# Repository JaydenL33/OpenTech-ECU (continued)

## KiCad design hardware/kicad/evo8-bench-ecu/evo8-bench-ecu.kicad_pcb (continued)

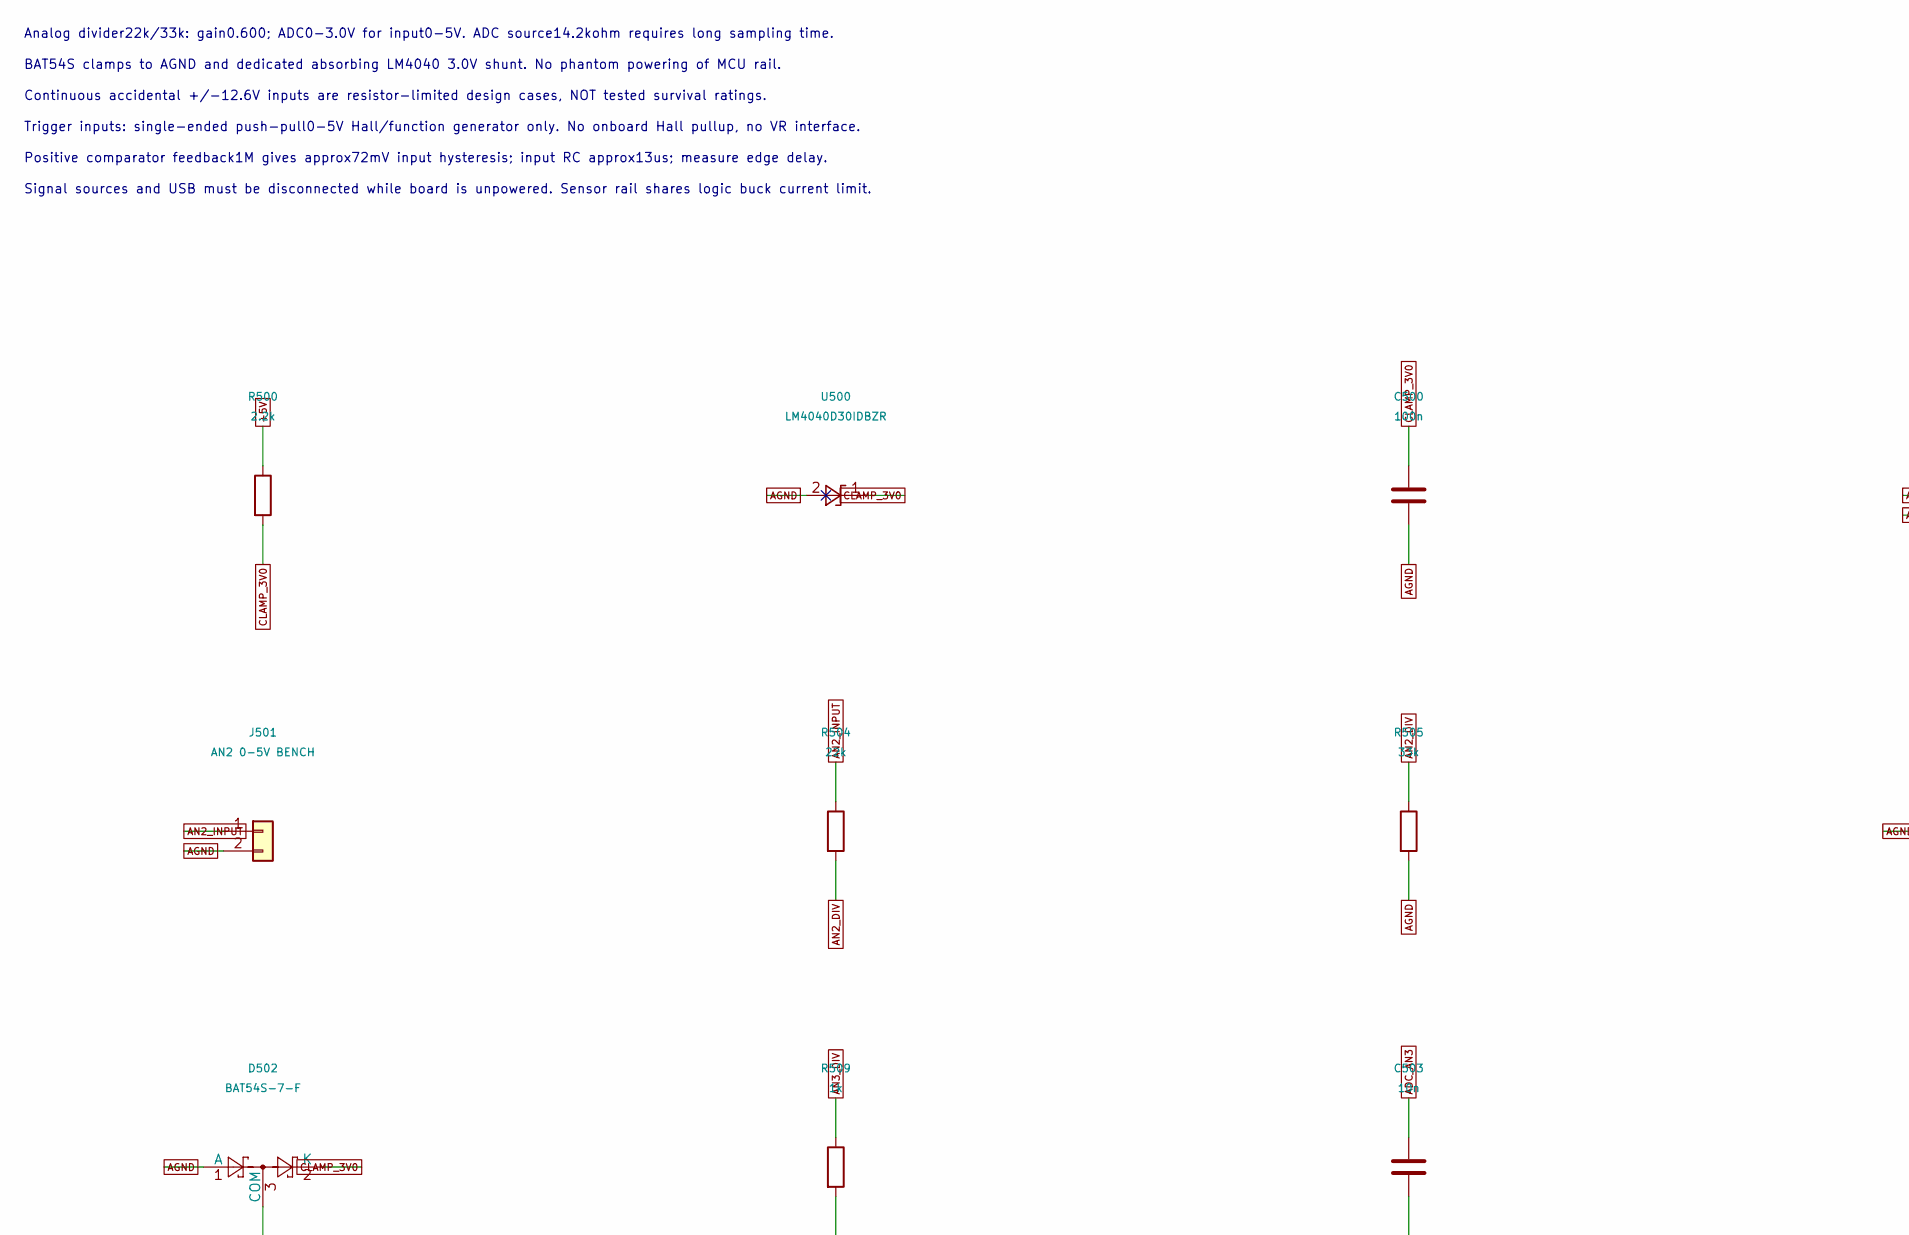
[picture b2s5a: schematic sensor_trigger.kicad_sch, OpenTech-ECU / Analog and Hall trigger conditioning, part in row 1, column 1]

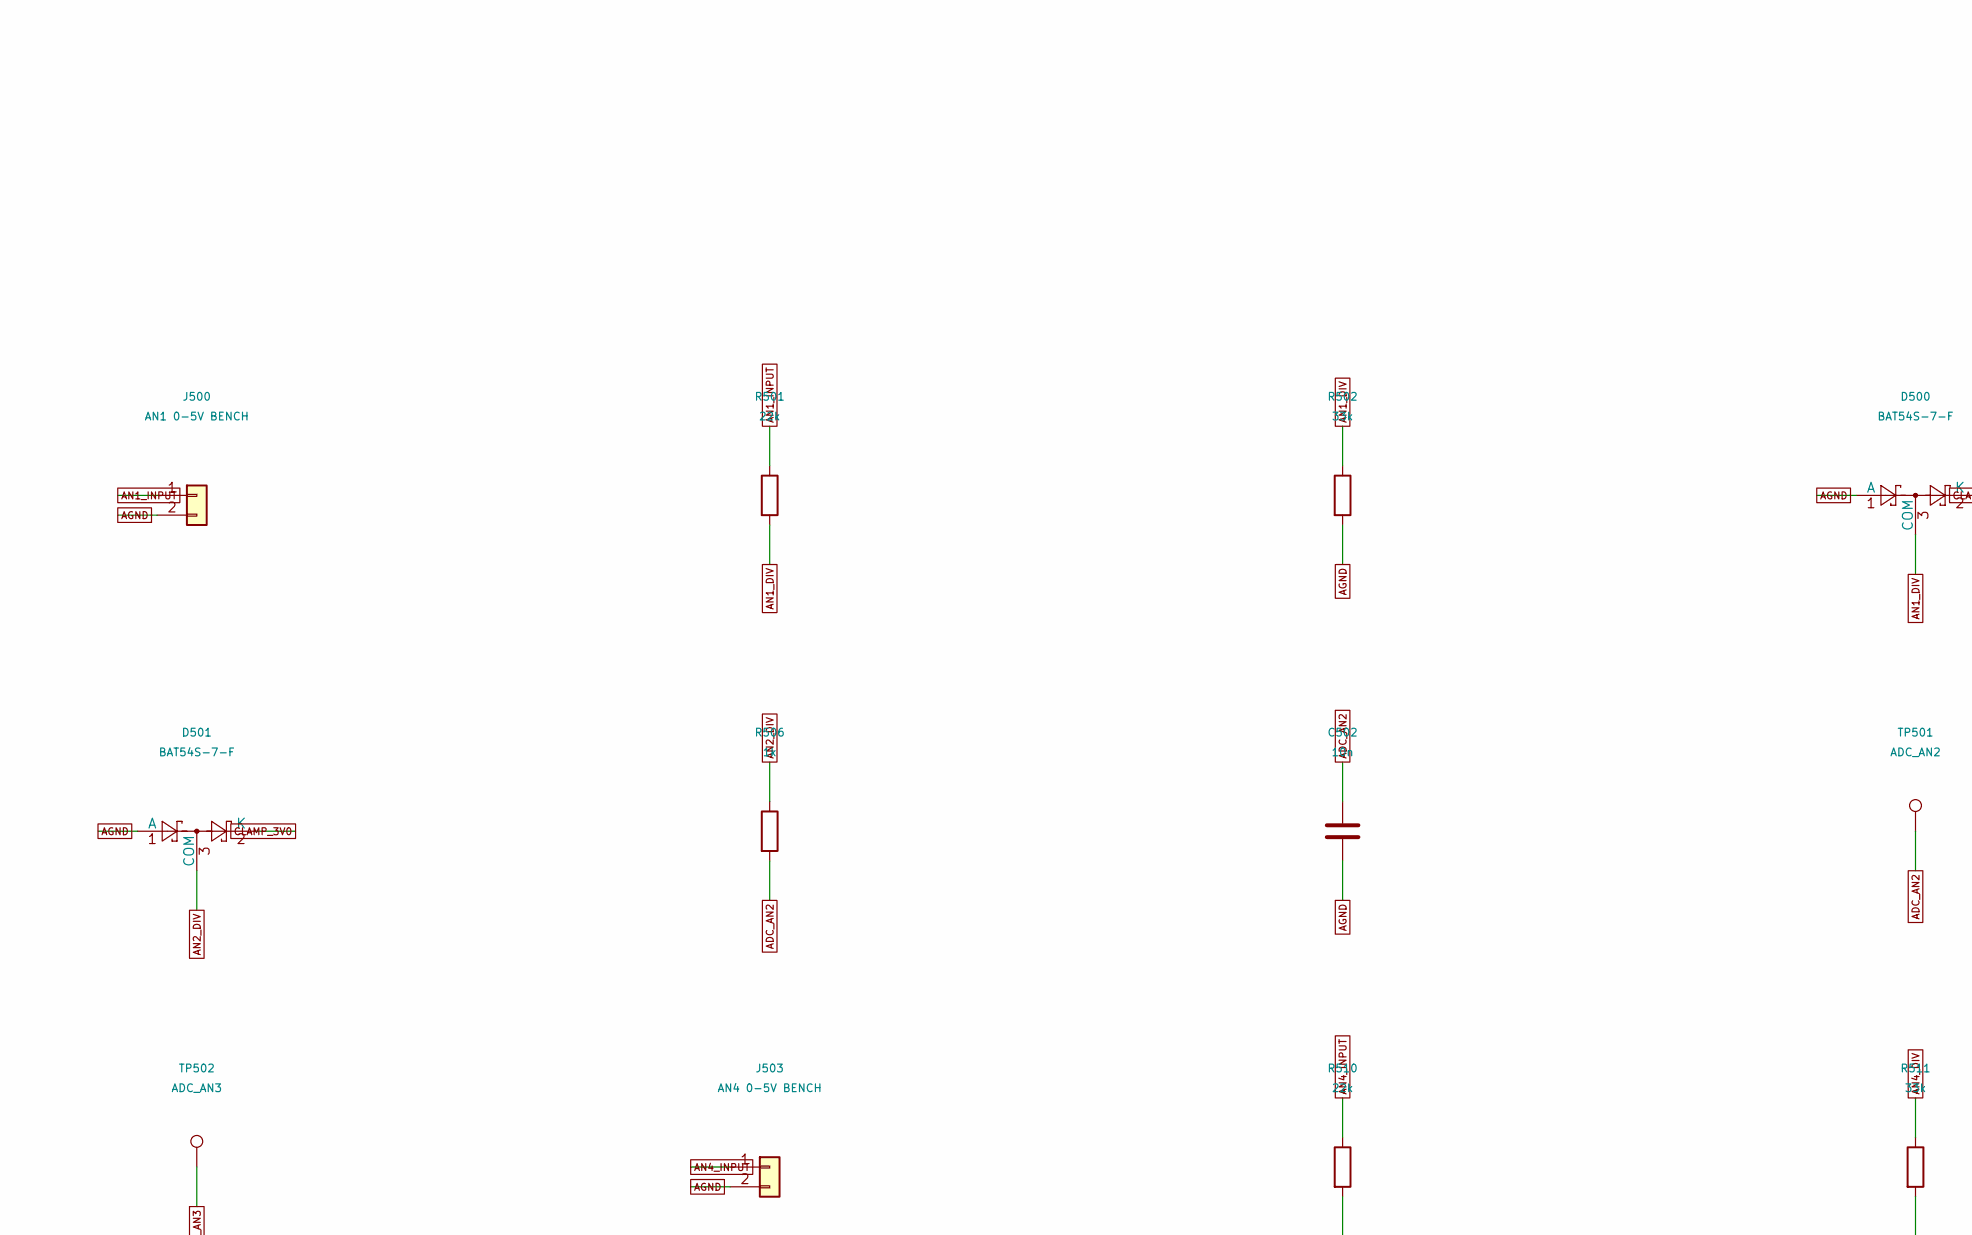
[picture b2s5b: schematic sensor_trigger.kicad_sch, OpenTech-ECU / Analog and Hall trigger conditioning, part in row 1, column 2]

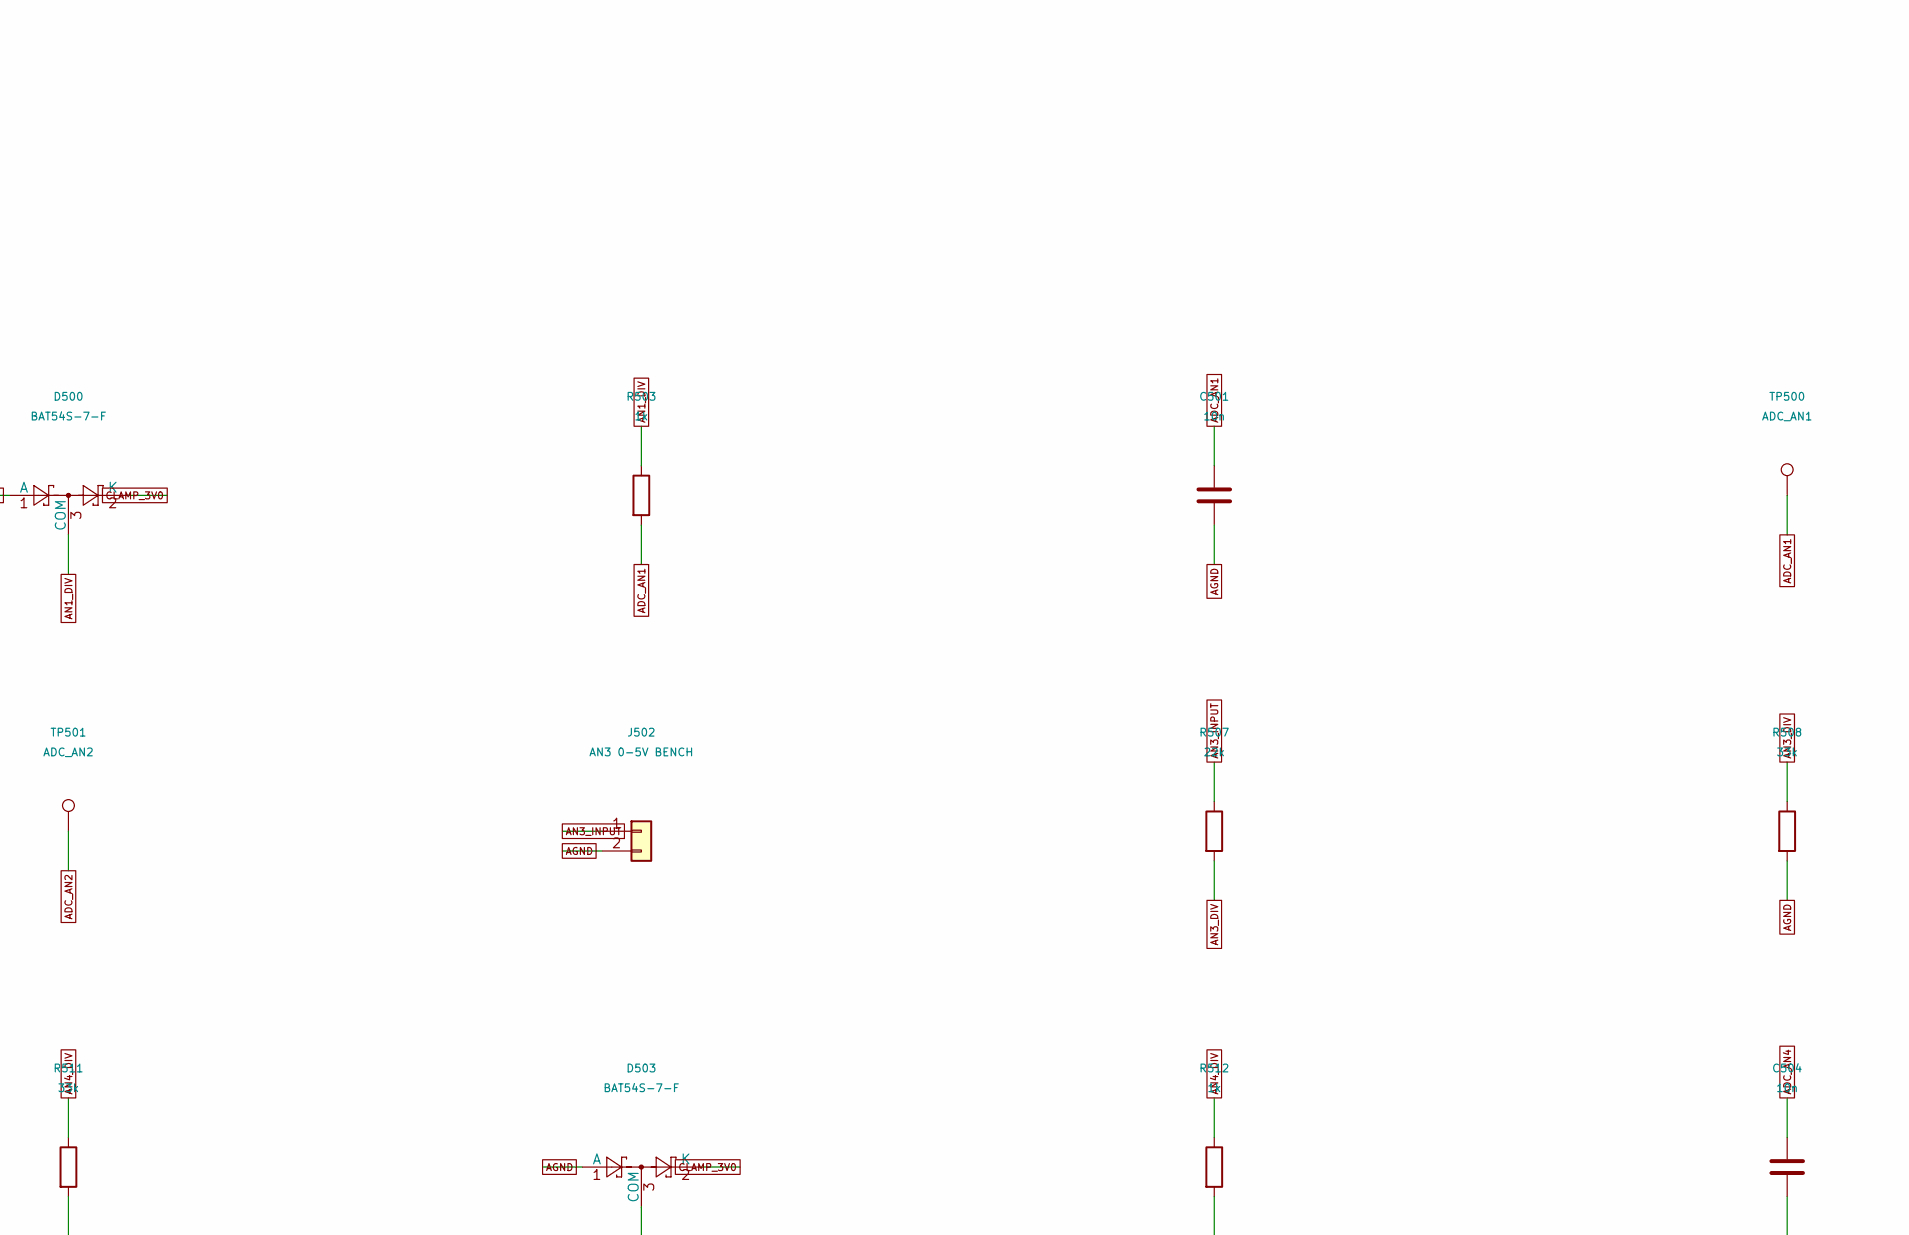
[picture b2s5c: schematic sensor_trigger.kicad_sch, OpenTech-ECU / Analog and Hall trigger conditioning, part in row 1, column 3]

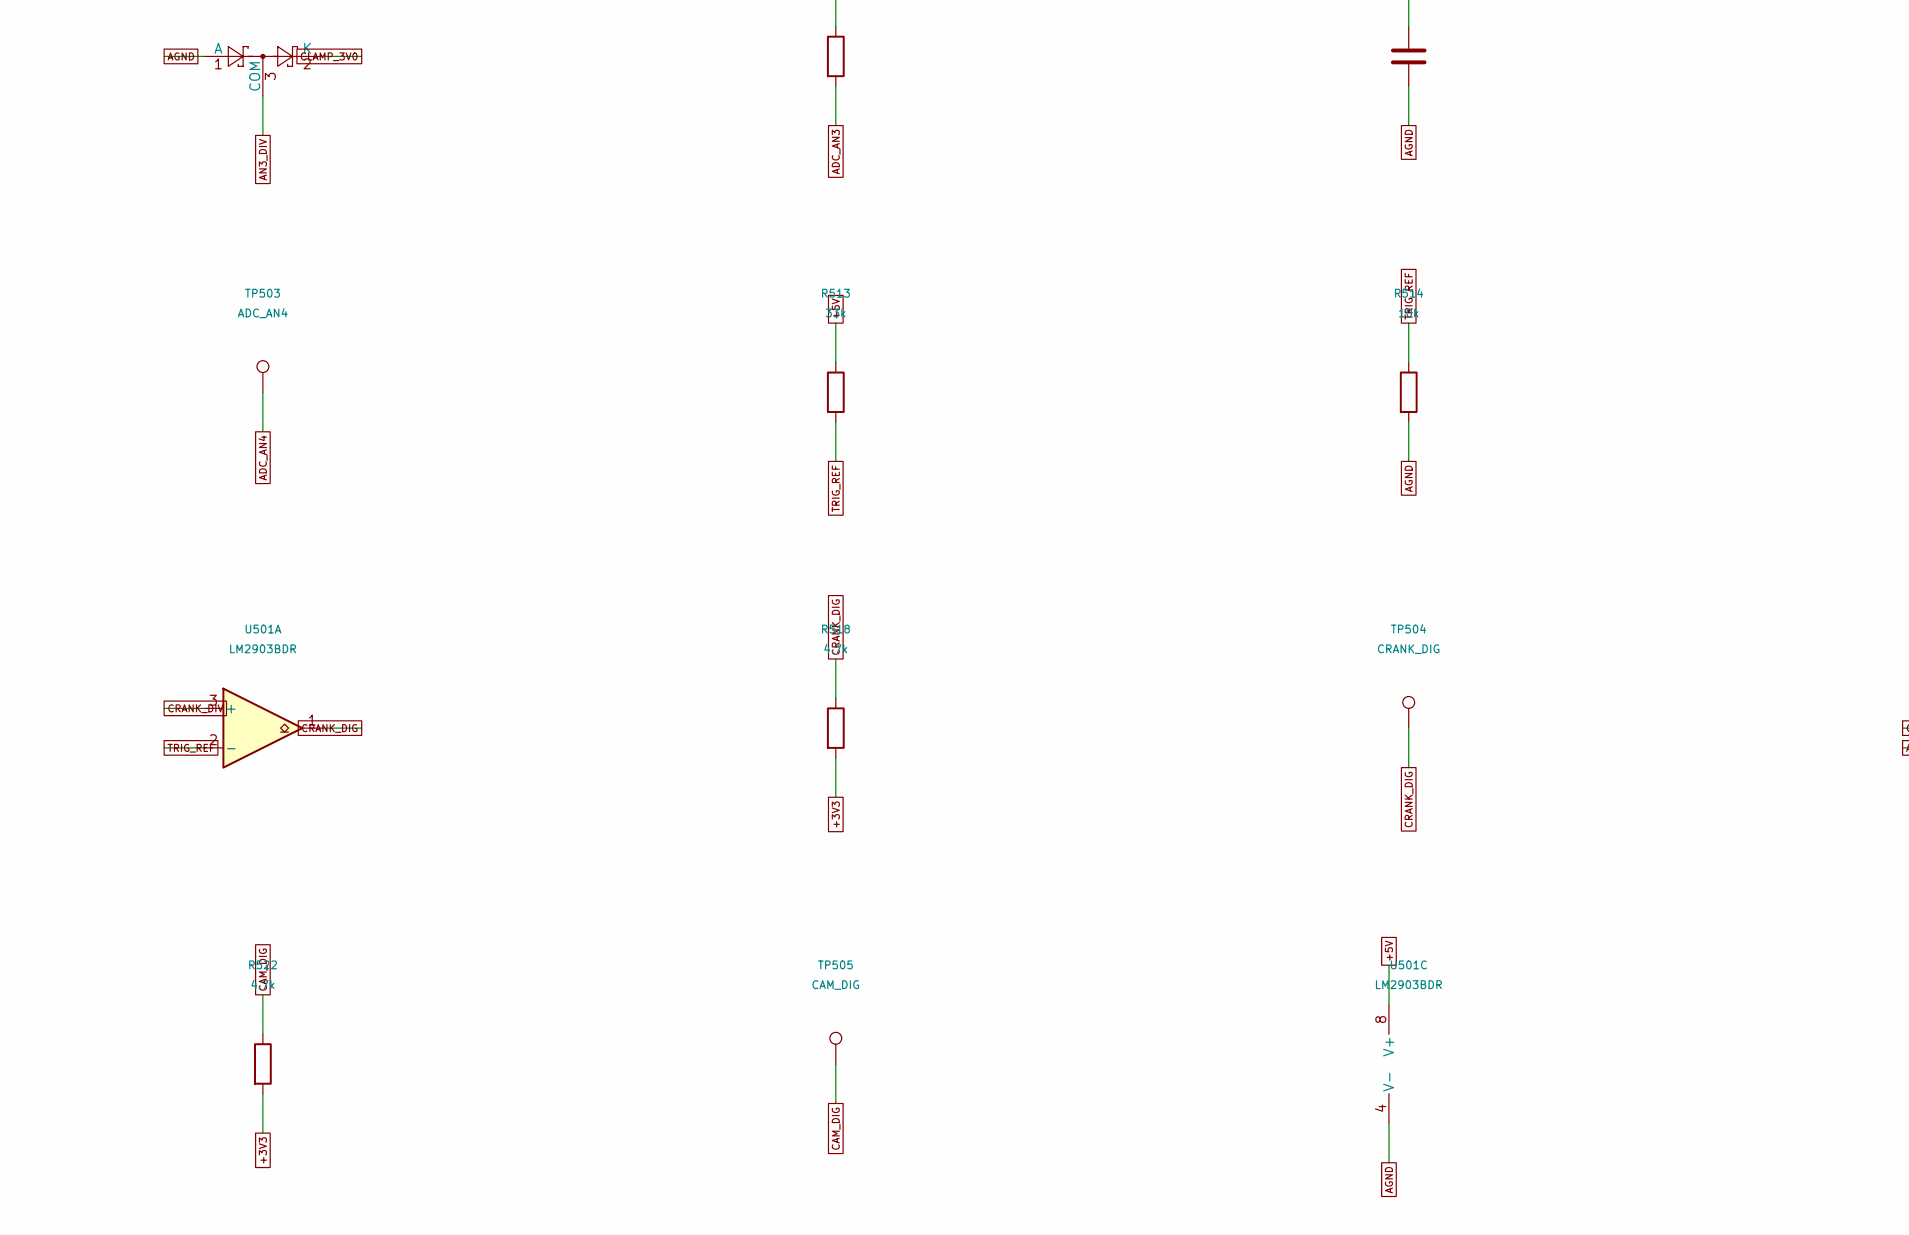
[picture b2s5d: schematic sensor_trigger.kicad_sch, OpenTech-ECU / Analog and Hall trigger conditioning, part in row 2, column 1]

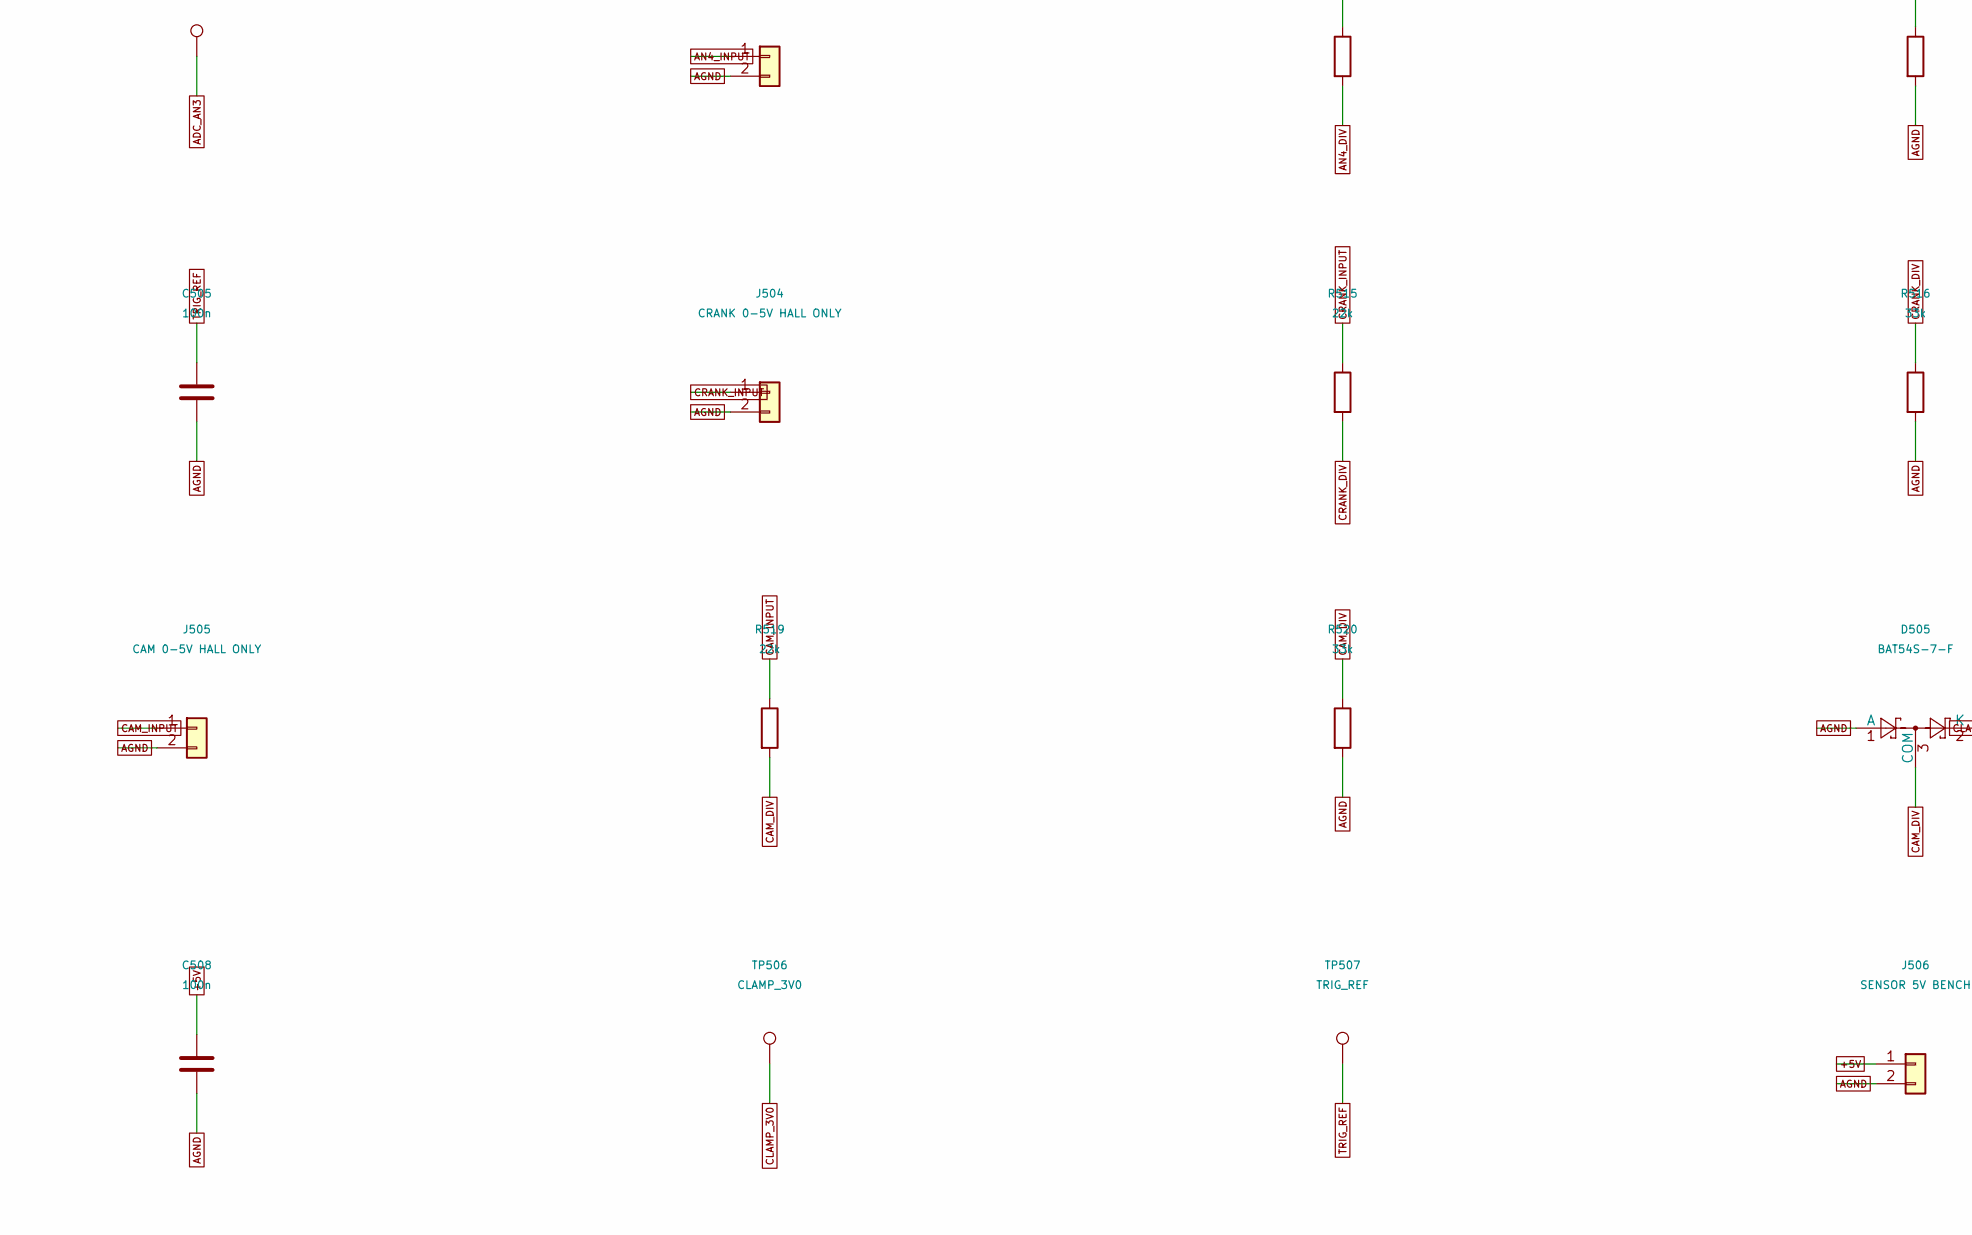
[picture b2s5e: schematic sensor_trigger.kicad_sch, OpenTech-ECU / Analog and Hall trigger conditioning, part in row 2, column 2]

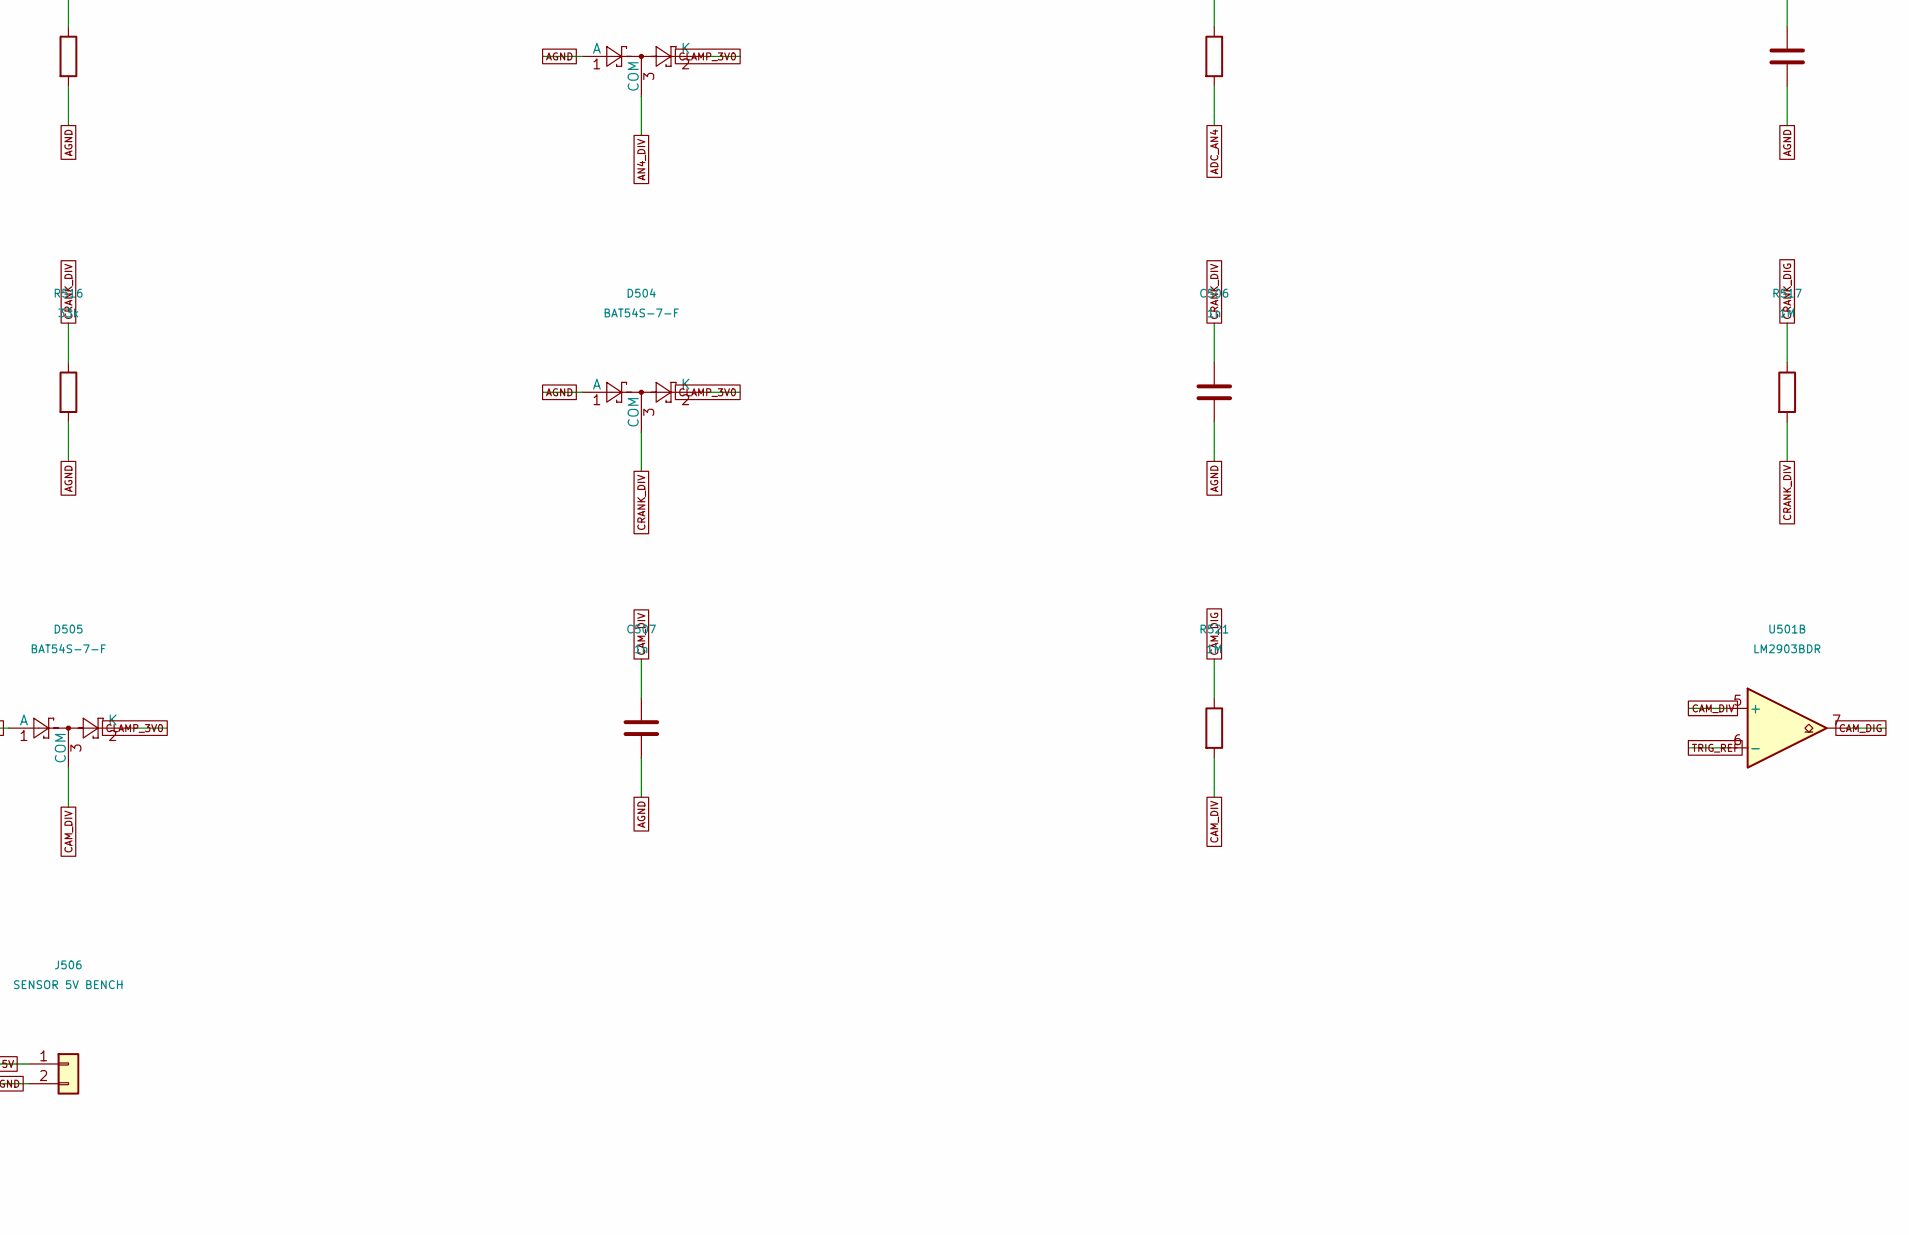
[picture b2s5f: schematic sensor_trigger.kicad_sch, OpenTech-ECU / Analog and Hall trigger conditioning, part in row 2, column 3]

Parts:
C500, C505, C508: 100n; C_0805_2012Metric; MPN GRM21BR71H104KA01L
C501, C502, C503, C504: 10n; C_0805_2012Metric; MPN GRM21BR71H103KA01L
C506, C507: 1n; C_0805_2012Metric; MPN GRM21B5C1H102JA01L
D500, D501, D502, D503, D504, D505: BAT54S-7-F; SOT-23; MPN BAT54S-7-F
J500: AN1 0-5V BENCH; TerminalBlock_Phoenix_MKDS-1,5-2-5.08_1x02_P5.08mm_Horizont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; MPN 1715721
J501: AN2 0-5V BENCH; TerminalBlock_Phoenix_MKDS-1,5-2-5.08_1x02_P5.08mm_Horizont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; MPN 1715721
J502: AN3 0-5V BENCH; TerminalBlock_Phoenix_MKDS-1,5-2-5.08_1x02_P5.08mm_Horizont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; MPN 1715721
J503: AN4 0-5V BENCH; TerminalBlock_Phoenix_MKDS-1,5-2-5.08_1x02_P5.08mm_Horizont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; MPN 1715721
J504: CRANK 0-5V HALL ONLY; TerminalBlock_Phoenix_MKDS-1,5-2-5.08_1x02_P5.08mm_Horizont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; MPN 1715721
J505: CAM 0-5V HALL ONLY; TerminalBlock_Phoenix_MKDS-1,5-2-5.08_1x02_P5.08mm_Horizont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; MPN 1715721
J506: SENSOR 5V BENCH; TerminalBlock_Phoenix_MKDS-1,5-2-5.08_1x02_P5.08mm_Horizont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; MPN 1715721
R500: 2.2k; R_0805_2012Metric; MPN RC0805FR-072K2L
R501, R504, R507, R510, R515, R519: 22k; R_0805_2012Metric; MPN RC0805FR-0722KL
R502, R505, R508, R511, R513, R516, R520: 33k; R_0805_2012Metric; MPN RC0805FR-0733KL
R503, R506, R509, R512: 1k; R_0805_2012Metric; MPN RC0805FR-071KL
R514: 10k; R_0805_2012Metric; MPN RC0805FR-0710KL
R517, R521: 1M; R_0805_2012Metric; MPN RC0805FR-071ML
R518, R522: 4.7k; R_0805_2012Metric; MPN RC0805FR-074K7L
TP500: ADC_AN1; TestPoint_THTPad_D2.0mm_Drill1.0mm; MPN 5010
TP501: ADC_AN2; TestPoint_THTPad_D2.0mm_Drill1.0mm; MPN 5010
TP502: ADC_AN3; TestPoint_THTPad_D2.0mm_Drill1.0mm; MPN 5010
TP503: ADC_AN4; TestPoint_THTPad_D2.0mm_Drill1.0mm; MPN 5010
TP504: CRANK_DIG; TestPoint_THTPad_D2.0mm_Drill1.0mm; MPN 5010
TP505: CAM_DIG; TestPoint_THTPad_D2.0mm_Drill1.0mm; MPN 5010
TP506: CLAMP_3V0; TestPoint_THTPad_D2.0mm_Drill1.0mm; MPN 5010
TP507: TRIG_REF; TestPoint_THTPad_D2.0mm_Drill1.0mm; MPN 5010
U500: LM4040D30IDBZR; SOT-23; MPN LM4040D30IDBZR
U501: LM2903BDR; SOIC-8_3.9x4.9mm_P1.27mm; MPN LM2903BDR

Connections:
+3V3: R518.2, R522.2; also elsewhere on the board
+5V: C508.1, J506.1, R500.1, R513.1, U501.8 (V+); also elsewhere on the board
ADC_AN1: C501.1, R503.2, TP500.1; also elsewhere on the board
ADC_AN2: C502.1, R506.2, TP501.1; also elsewhere on the board
ADC_AN3: C503.1, R509.2, TP502.1; also elsewhere on the board
ADC_AN4: C504.1, R512.2, TP503.1; also elsewhere on the board
AGND: C500.2, C501.2, C502.2, C503.2, C504.2, C505.2, C506.2, C507.2, C508.2, D500.1 (A), D501.1 (A), D502.1 (A), D503.1 (A), D504.1 (A), D505.1 (A), J500.2, J501.2, J502.2, J503.2, J504.2, J505.2, J506.2, R502.2, R505.2, R508.2, R511.2, R514.2, R516.2, R520.2, U500.2 (A), U501.4 (V-); also elsewhere on the board
AN1_DIV: D500.3 (COM), R501.2, R502.1, R503.1
AN1_INPUT: J500.1, R501.1
AN2_DIV: D501.3 (COM), R504.2, R505.1, R506.1
AN2_INPUT: J501.1, R504.1
AN3_DIV: D502.3 (COM), R507.2, R508.1, R509.1
AN3_INPUT: J502.1, R507.1
AN4_DIV: D503.3 (COM), R510.2, R511.1, R512.1
AN4_INPUT: J503.1, R510.1
CAM_DIG: R521.1, R522.1, TP505.1, U501.7; also elsewhere on the board
CAM_DIV: C507.1, D505.3 (COM), R519.2, R520.1, R521.2, U501.5 (+)
CAM_INPUT: J505.1, R519.1
CLAMP_3V0: C500.1, D500.2 (K), D501.2 (K), D502.2 (K), D503.2 (K), D504.2 (K), D505.2 (K), R500.2, TP506.1, U500.1 (K)
CRANK_DIG: R517.1, R518.1, TP504.1, U501.1; also elsewhere on the board
CRANK_DIV: C506.1, D504.3 (COM), R515.2, R516.1, R517.2, U501.3 (+)
CRANK_INPUT: J504.1, R515.1
TRIG_REF: C505.1, R513.2, R514.1, TP507.1, U501.2 (-), U501.6 (-)

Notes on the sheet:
Analog divider22k/33k: gain0.600; ADC0-3.0V for input0-5V. ADC source14.2kohm requires long sampling time.
BAT54S clamps to AGND and dedicated absorbing LM4040 3.0V shunt. No phantom powering of MCU rail.
Continuous accidental +/-12.6V inputs are resistor-limited design cases, NOT tested survival ratings.
Trigger inputs: single-ended push-pull0-5V Hall/function generator only. No onboard Hall pullup, no VR interface.
Positive comparator feedback1M gives approx72mV input hysteresis; input RC approx13us; measure edge delay.
Signal sources and USB must be disconnected while board is unpowered. Sensor rail shares logic buck current limit.
